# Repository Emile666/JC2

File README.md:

# Junior Computer 2 (JC ][)
Junior-Computer-2 Hardware and Software projects.

# History
The Junior computer design was published by Elektuur/Elektor from 1980 on. It was developed by Loys Nachtmann. The Junior computer is more or less a copy of the original KIM-1 single board computer.

Fourty years later, Joerg Walke created the Junior-Computer 2, which is an expanded version of the original Junior Computer. It contained 32 KB RAM, 8KB ROM and an onboard RS232 serial interface. The development of the Junior Computer 2 is still in progress and you can read all about it on the web-site of Joerg: https://old-computer-tech.net/junior-computer/

Up until now Joerg created the JC2-board (v3.1b), the IO-Basic card, the JC2 backplane card and the Floppy-Graphics (FGC) card.

I became enthusiastic about all the excellent hardware and software Joerg developed and decided to built these boards and then to create add-ons, both hardware and software.

This page serves as a placeholder for all hardware and software projects that I created. It is all open-source, so enjoy!

# Hardware projects

Hardware projects are (mostly) created with KiCad 8 and I publish both the KiCad project-files as the Gerber files. The Gerber files can be sent directly to a PCB manufacturer.

Since these projects nearly always contain a GAL or CPLD, the .pld files describing the programmable logic is also included. I typically use an ATF16V8, an ATF22V10 or an ATF1504 (plcc44 and plcc84). They are programmed with WinCUPL and the .pld file can be loaded directly into WinCUPL. The resulting .jed file is either programmed into the GAL / CPLD directly with the Afterburner programmer (ATF16V8 and ATF22V10), or further processed by ATMISP (to create a .svf file from the .jed file) and svf2xsvf502 (to create a .xsvf file from the .svf file) and then programmed by the Afterburner programmer into the device (ATF1504). A detailed walk-through for an ATF1504 is found [here](./atf1504_program_aftb.md).

- [RAM-bank add-on](./Hardware/rambank): I created a 512K add-on board for the JC2 which contains a AS6C4008 512Kx8 SRAM and a ATF1504 plcc44 GAL. It contains a memory management unit (MMU) register that can switch Monitor ROM, BIOS ROM and the different RAM-banks (28 banks of 16K each). Current version is made with Eagle, never revisions are planned to be made with KiCad.
- [Compact-Flash IDE interface](./Hardware/cf_ide): The idea originated from the Atari XL CF-IDE interface. I changed it for the JC2. Most of the TTL ICs were removed and put into a GAL (an ATF16V8).
- [Backplane](./Hardware/backplane/): I created an update of Joerg's original backplane and added a flat-cable connector to it, so that you can have multiple backplanes connected together.
- [Main-Board](./Hardware/main_board/): I created an update of Joerg's original v3.1b main-board, most notable changes are: 1) one integrated eprom combining Monitor, Basic and BIOS 2) ATF1504 MMU added that supports 512K RAM with 28 RAM-banks of 16K each 3) Monitor, BIOS and Basic ROM are now switchable from MMU, enabling RAM behind it 4) Additional 6522 VIA 5) UART-to-USB bridge added.
- [IO2-Board](./Hardware/IO2/): I created an update of Joerg's original rev. 1D IO-board, most notable changes are: 1) BASIC eprom moved to JC2 main-board and removed all diode-based logic 2) removed papertape reader, Datasette interface and ASCII-keyboard 3) Added 3 x 16-bits IO with MCP23017 ICs 4) Added SPI RAM (1024 Kb)  and I2C eeprom (512 Kb) 5) Added PCF8591 8-bit ADC and DAC 6) Added One-Wire Interface with DS2482 7) Added CF-IDE Interface 8) Level-shifting with BSS138 board instead of 74LVC245.

# Software projects

Software projects are written in 6502 assembly language and are assembled with the Mad-Assembler (MADS), https://mads.atari8.info/. I call MADS from the Windows command-line with mads <filename.asm> -l:<filename.lst> -o:<filename.bin>. This makes sure that you get a decent list-file and the .bin file that can be uploaded to the JC2 using the XMODEM protocol.

- [Memory-test](./Software/memtest): The memory-test program scans the hardware present and detects if a MMU is present. It shows and tests all available RAM and ROM memory, displays the number of RAM-banks found and tests each one of them.
- [Monitor](./Software/jc2_mon_1K): This is the original monitor program written by A. Nachtmann (1980), which was restored and adapted for TASM by A.J. Prosman (2019). I adapted the source for MADS (2024). Included here for reference.
- [JC2-DOS65](./Software/jc2_dos65): Joerg made a v0.2.0 version that supported the SD-card. This version here is a further development and now supports the CF-IDE Interface.
- [JC2-1-EPROM](./Software/jc2_1_eprom): This software integrates BASIC, BIOS and Monitor ROM into a single EPROM version. It already includes the CF-IDE drivers and is supported by a RAM-loader for testing without directly creating a new EPROM version.

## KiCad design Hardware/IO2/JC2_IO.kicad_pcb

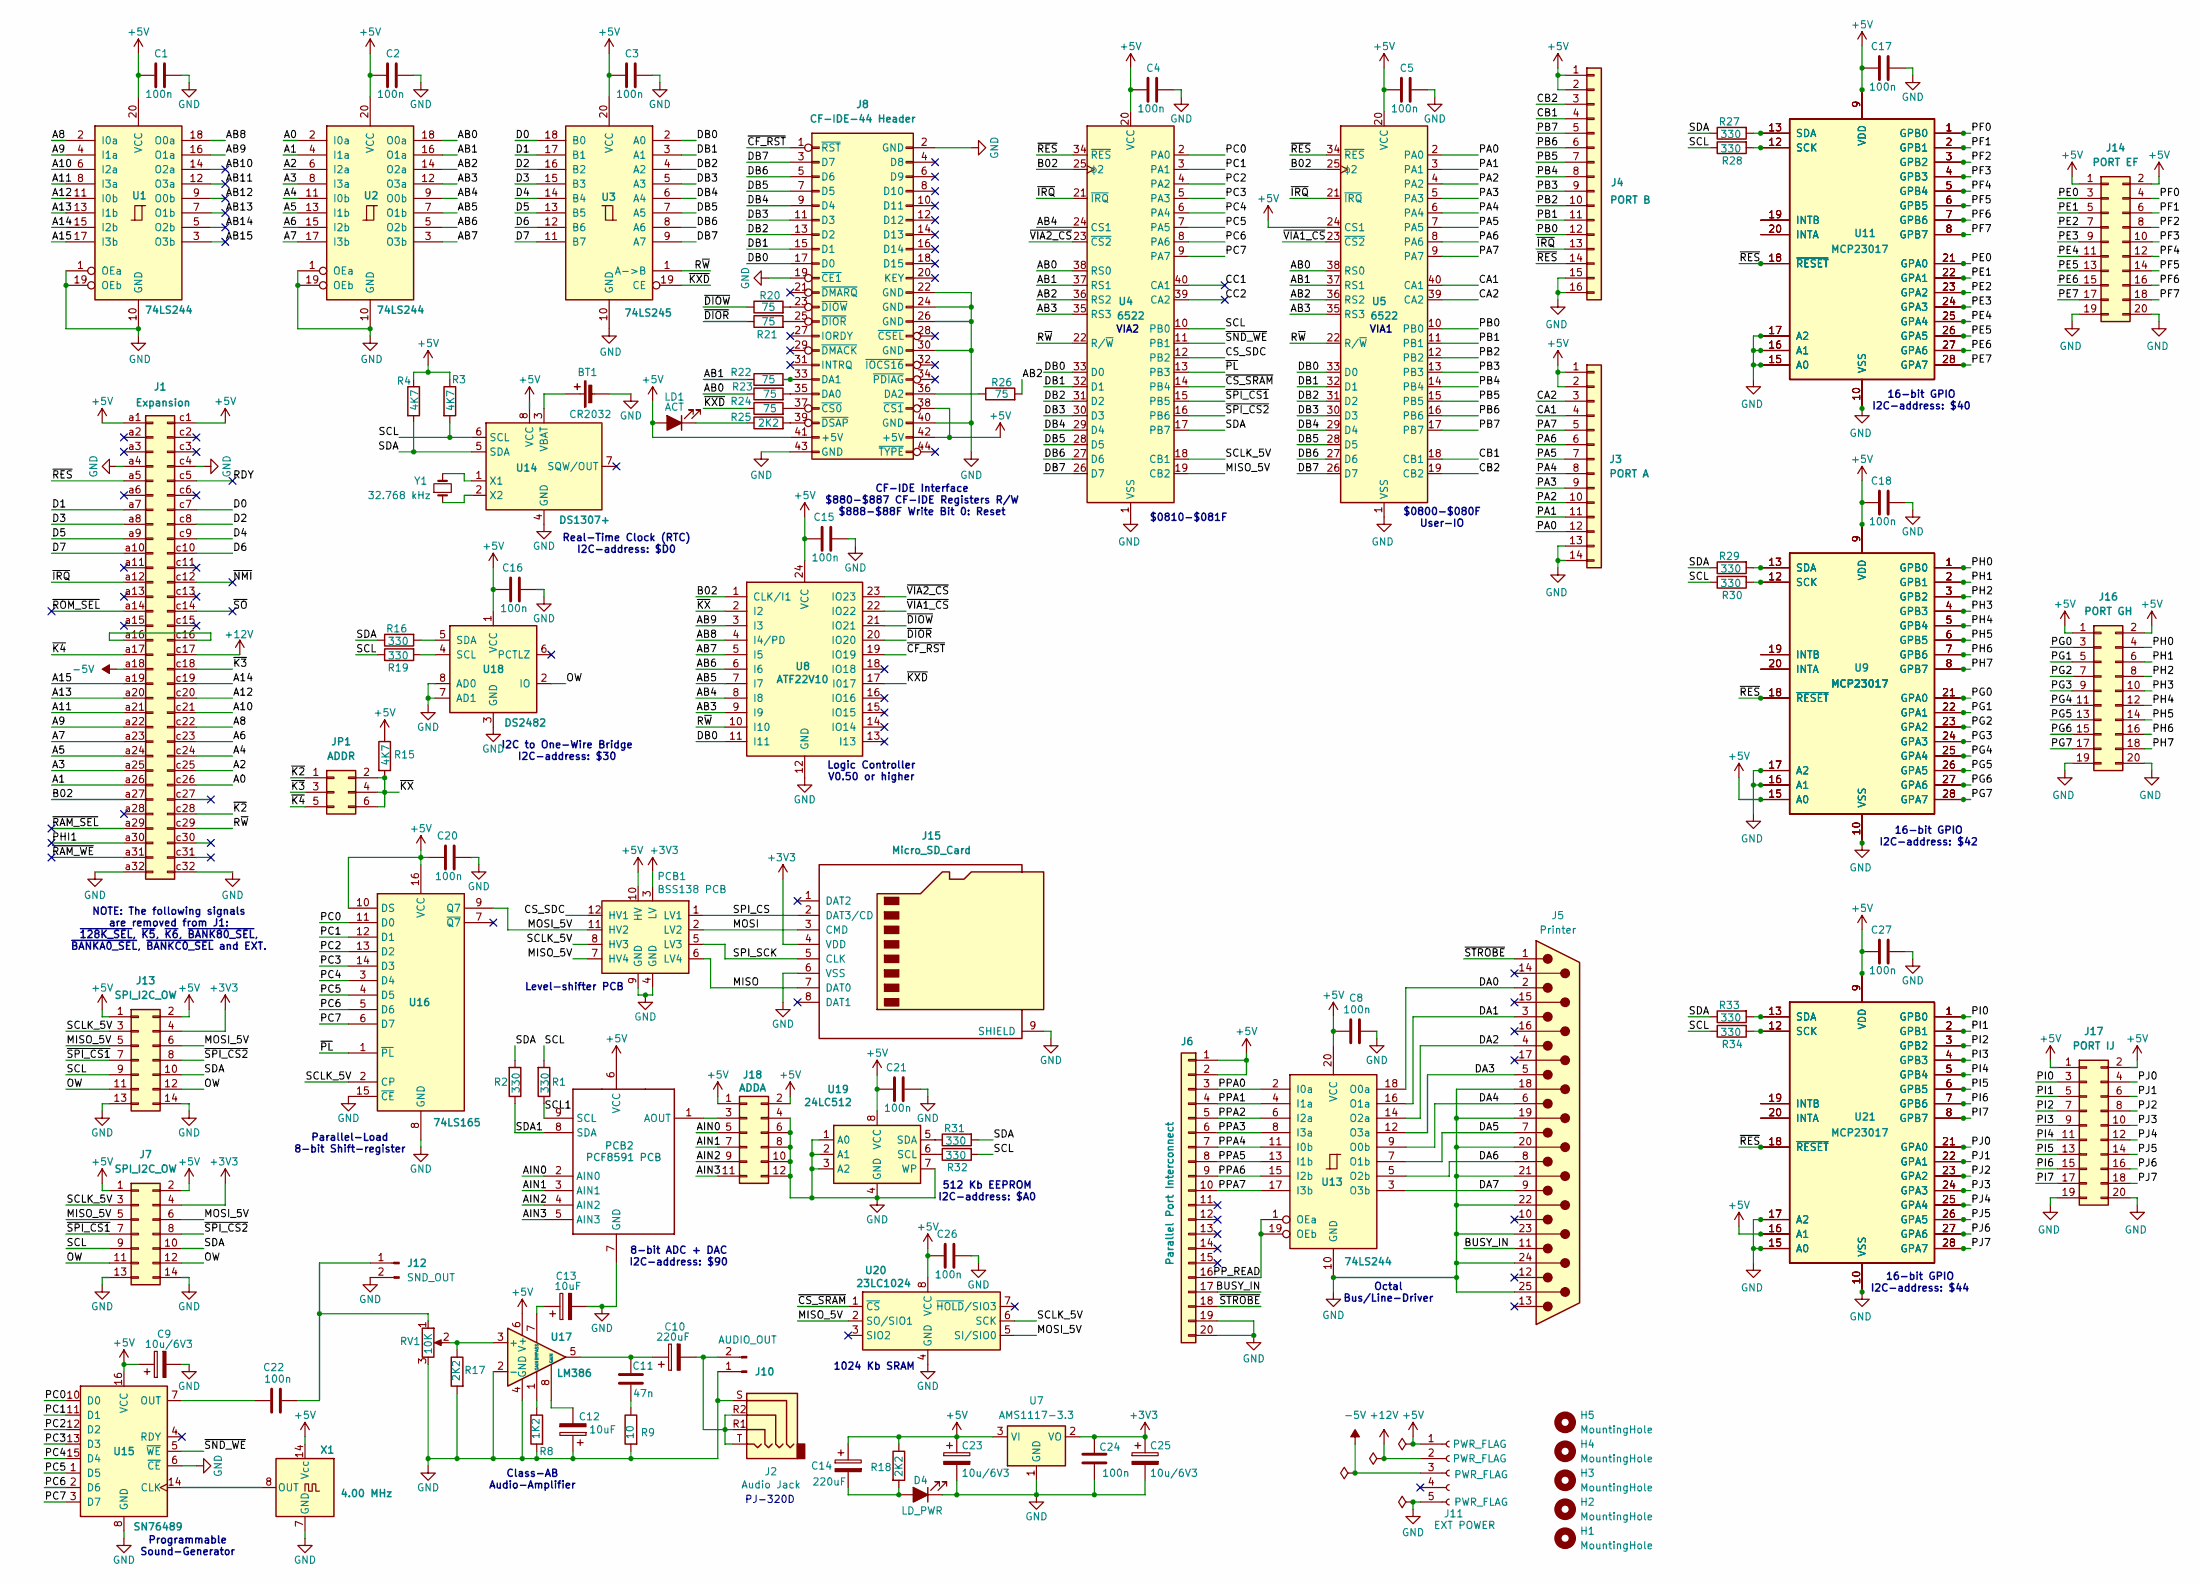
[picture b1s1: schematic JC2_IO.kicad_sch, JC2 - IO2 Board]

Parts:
BT1: CR2032; BatteryHolder_Keystone_107_1x23mm
C1, C2, C3, C4, C5, C8, C15, C16, C17, C18, C20, C21, C22, C24, C26, C27: 100n; C_Rect_L4.6mm_W2.0mm_P2.50mm_MKS02_FKP02
C9, C23, C25: 10u/6V3; CP_Radial_D5.0mm_P2.00mm
C10, C14: 220uF; CP_Radial_D8.0mm_P5.00mm
C11: 47n; C_Rect_L4.6mm_W2.0mm_P2.50mm_MKS02_FKP02
C12, C13: 10uF; CP_Radial_D5.0mm_P2.00mm
D4: LD_PWR; LED_D3.0mm
H1, H2, H3, H4, H5: MountingHole; MountingHole_4.3mm_M4
J1: Expansion; DIN41612_C_2x32_Male_Horizontal_THT
J2: Audio Jack; Jack_3.5mm_PJ320D_Horizontal
J3: PORT A; PinSocket_2x07_P2.54mm_Horizontal
J4: PORT B; PinHeader_2x08_P2.54mm_Horizontal
J5: Printer; DSUB-25_Female_Horizontal_P2.77x2.84mm_EdgePinOffset4.94mm_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
J6: Parallel Port Interconnect; IDC-Header_2x10_P2.54mm_Vertical
J7, J13: SPI_I2C_OW; PinHeader_2x07_P2.54mm_Vertical
J8: CF-IDE-44 Header; PinHeader_2x22_P2.00mm_Vertical
J10: AUDIO_OUT; PinHeader_2x01_P2.54mm_Vertical
J11: EXT POWER; PinHeader_1x05_P2.54mm_Vertical
J12: SND_OUT; PinHeader_2x01_P2.54mm_Vertical
J14: PORT EF; PinHeader_2x10_P2.54mm_Vertical
J15: Micro_SD_Card; SD_Card-micro_socket_A
J16: PORT GH; PinHeader_2x10_P2.54mm_Vertical
J17: PORT IJ; PinHeader_2x10_P2.54mm_Vertical
J18: ADDA; PinHeader_2x06_P2.54mm_Vertical
JP1: ADDR; PinHeader_2x03_P2.54mm_Vertical
LD1: ACT; LED_1206_3216Metric_Pad1.42x1.75mm_HandSolder
PCB1: BSS138 PCB; DIP-12_W10.16mm
PCB2: PCF8591 PCB; PCF8591_PCB
R1, R2, R16, R19, R27, R28, R29, R30, R31, R32, R33, R34: 330; R_Axial_DIN0207_L6.3mm_D2.5mm_P10.16mm_Horizontal
R3, R4, R15: 4K7; R_Axial_DIN0207_L6.3mm_D2.5mm_P10.16mm_Horizontal
R8: 1K2; R_Axial_DIN0207_L6.3mm_D2.5mm_P10.16mm_Horizontal
R9: 10; R_Axial_DIN0207_L6.3mm_D2.5mm_P10.16mm_Horizontal
R17, R18: 2K2; R_Axial_DIN0207_L6.3mm_D2.5mm_P10.16mm_Horizontal
R20, R21, R22, R23, R24, R26: 75; R_1206_3216Metric_Pad1.30x1.75mm_HandSolder
R25: 2K2; R_1206_3216Metric_Pad1.30x1.75mm_HandSolder
RV1: 10K; Potentiometer_ACP_CA14-H5_Horizontal
U1, U2, U13: 74LS244; DIP-20_W7.62mm_Socket
U3: 74LS245; DIP-20_W7.62mm_Socket
U4, U5: 6522; DIP-40_W15.24mm
U7: AMS1117-3.3; SOT-223-3_TabPin2
U8: ATF22V10; DIP-24_W7.62mm
U9, U11, U21: MCP23017; DIP-28_W7.62mm
U14: DS1307+; DIP-8_W7.62mm
U15: SN76489; CERDIP-16_W7.62mm_SideBrazed_Socket
U16: 74LS165; DIP-16_W7.62mm
U17: LM386; DIP-8_W7.62mm
U18: DS2482; SOIC-8W_5.3x5.3mm_P1.27mm
U19: 24LC512; DIP8_SOIC8
U20: 23LC1024; DIP8_SOIC8
U22: MCP23017; SOIC-28W_7.5x18.7mm_P1.27mm
U23, U24: MCP23017_SO; SOIC-28W_7.5x17.9mm_P1.27mm
X1: 4.00 MHz; Oscillator_DIP-14
Y1: 32.768 kHz; Crystal_C38-LF_D3.0mm_L8.0mm_Horizontal

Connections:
+3V3: C24.1, C25.1, J7.4, J13.4, J15.4 (VDD), PCB1.3 (LV), U7.2 (VO)
+5V: C1.1, C2.1, C3.1, C4.1, C5.1, C8.1, C9.1, C14.1, C15.1, C16.1, C17.1, C18.1, C20.1, C21.1, C23.1, C26.1, C27.1, J1.a1, J1.c1, J3.1, J3.2, J4.1, J4.2, J6.1, J6.2, J7.1, J7.2, J8.38 (~CS1), J8.41 (+5V), J8.42 (+5V), J11.1, J13.1, J13.2, J14.1, J14.2, J16.1, J16.2, J17.1, J17.2, J18.1, J18.2, LD1.2 (A), PCB1.10 (HV), PCB2.6 (VCC), R3.1, R4.1, R15.1, R18.1, U1.20 (VCC), U2.20 (VCC), U3.20 (VCC), U4.20 (VCC), U5.20 (VCC), U5.24 (CS1), U7.3 (VI), U8.24 (VCC), U9.9 (VDD), U9.15 (A0), U11.9 (VDD), U13.20 (VCC), U14.8 (VCC), U15.16 (VCC), U16.10 (DS), U16.16 (VCC), U17.6 (V+), U18.1 (VCC), U19.8 (VCC), U20.8 (VCC), U21.9 (VDD), U21.16 (A1), U22.9 (VDD), U22.15 (A0), U23.9 (VDD), U23.16 (A1), U24.9 (VDD), X1.14 (Vcc)
+12V: J1.c17, J11.2
-5V: J1.a18, J11.3
/A0: J1.c26, U2.2 (I0a)
/A1: J1.a26, U2.4 (I1a)
/A2: J1.c25, U2.6 (I2a)
/A3: J1.a25, U2.8 (I3a)
/A4: J1.c24, U2.11 (I0b)
/A5: J1.a24, U2.13 (I1b)
/A6: J1.c23, U2.15 (I2b)
/A7: J1.a23, U2.17 (I3b)
/A8: J1.c22, U1.2 (I0a)
/A9: J1.a22, U1.4 (I1a)
/A10: J1.c21, U1.6 (I2a)
/A11: J1.a21, U1.8 (I3a)
/A12: J1.c20, U1.11 (I0b)
/A13: J1.a20, U1.13 (I1b)
/A14: J1.c19, U1.15 (I2b)
/A15: J1.a19, U1.17 (I3b)
/AB0: R23.1, U2.18 (O0a), U4.38 (RS0), U5.38 (RS0)
/AB1: R22.1, U2.16 (O1a), U4.37 (RS1), U5.37 (RS1)
/AB2: R26.2, U2.14 (O2a), U4.36 (RS2), U5.36 (RS2)
/AB3: U2.12 (O3a), U4.35 (RS3), U5.35 (RS3), U8.9 (I9)
/AB4: U2.9 (O0b), U4.24 (CS1), U8.8 (I8)
/AB5: U2.7 (O1b), U8.7 (I7)
/AB6: U2.5 (O2b), U8.6 (I6)
/AB7: U2.3 (O3b), U8.5 (I5)
/AB8: U1.18 (O0a), U8.4 (I4/PD)
/AB9: U1.16 (O1a), U8.3 (I3)
/AB10: U1.14 (O2a)
/AB11: U1.12 (O3a)
/AB12: U1.9 (O0b)
/AB13: U1.7 (O1b)
/AB14: U1.5 (O2b)
/AB15: U1.3 (O3b)
/AIN0: J18.5, PCB2.2 (AIN0)
/AIN1: J18.7, PCB2.3 (AIN1)
/AIN2: J18.9, PCB2.4 (AIN2)
/AIN3: J18.11, PCB2.5 (AIN3)
/B02: J1.a27, U4.25 (ϕ2), U5.25 (ϕ2), U8.1 (CLK/I1)
/BUSY_IN: J5.11, J6.17
/CA1: J3.4, U5.40 (CA1)
/CA2: J3.3, U5.39 (CA2)
/CB1: J4.4, U5.18 (CB1)
/CB2: J4.3, U5.19 (CB2)
/CC1: U4.40 (CA1)
/CC2: U4.39 (CA2)
/CS_SDC: PCB1.12 (HV1), U4.12 (PB2)
/D0: J1.c7, U3.18 (B0)
/D1: J1.a7, U3.17 (B1)
/D2: J1.c8, U3.16 (B2)
/D3: J1.a8, U3.15 (B3)
/D4: J1.c9, U3.14 (B4)
/D5: J1.a9, U3.13 (B5)
/D6: J1.c10, U3.12 (B6)
/D7: J1.a10, U3.11 (B7)
/DA0: J5.2, U13.18 (O0a)
/DA1: J5.3, U13.16 (O1a)
/DA2: J5.4, U13.14 (O2a)
/DA3: J5.5, U13.12 (O3a)
/DA4: J5.6, U13.9 (O0b)
/DA5: J5.7, U13.7 (O1b)
/DA6: J5.8, U13.5 (O2b)
/DA7: J5.9, U13.3 (O3b)
/DB0: J8.17 (D0), U3.2 (A0), U4.33 (D0), U5.33 (D0), U8.11 (I11)
/DB1: J8.15 (D1), U3.3 (A1), U4.32 (D1), U5.32 (D1)
/DB2: J8.13 (D2), U3.4 (A2), U4.31 (D2), U5.31 (D2)
/DB3: J8.11 (D3), U3.5 (A3), U4.30 (D3), U5.30 (D3)
/DB4: J8.9 (D4), U3.6 (A4), U4.29 (D4), U5.29 (D4)
/DB5: J8.7 (D5), U3.7 (A5), U4.28 (D5), U5.28 (D5)
/DB6: J8.5 (D6), U3.8 (A6), U4.27 (D6), U5.27 (D6)
/DB7: J8.3 (D7), U3.9 (A7), U4.26 (D7), U5.26 (D7)
/MISO: J15.7 (DAT0), PCB1.6 (LV4)
/MISO_5V: J7.5, J13.5, PCB1.7 (HV4), U4.19 (CB2), U20.2 (SO/SIO1)
/MOSI: J15.3 (CMD), PCB1.2 (LV2)
/MOSI_5V: J7.6, J13.6, PCB1.11 (HV2), U16.9 (Q7), U20.5 (SI/SIO0)
/OW: J7.11, J7.12, J13.11, J13.12, U18.2 (IO)
/PA0: J3.12, U5.2 (PA0)
/PA1: J3.11, U5.3 (PA1)
/PA2: J3.10, U5.4 (PA2)
/PA3: J3.9, U5.5 (PA3)
/PA4: J3.8, U5.6 (PA4)
/PA5: J3.7, U5.7 (PA5)
/PA6: J3.6, U5.8 (PA6)
/PA7: J3.5, U5.9 (PA7)
/PB0: J4.12, U5.10 (PB0)
/PB1: J4.11, U5.11 (PB1)
/PB2: J4.10, U5.12 (PB2)
/PB3: J4.9, U5.13 (PB3)
/PB4: J4.8, U5.14 (PB4)
/PB5: J4.7, U5.15 (PB5)
/PB6: J4.6, U5.16 (PB6)
/PB7: J4.5, U5.17 (PB7)
/PC0: U4.2 (PA0), U15.10 (D0), U16.11 (D0)
/PC1: U4.3 (PA1), U15.11 (D1), U16.12 (D1)
/PC2: U4.4 (PA2), U15.12 (D2), U16.13 (D2)
/PC3: U4.5 (PA3), U15.13 (D3), U16.14 (D3)
/PC4: U4.6 (PA4), U15.15 (D4), U16.3 (D4)
/PC5: U4.7 (PA5), U15.1 (D5), U16.4 (D5)
/PC6: U4.8 (PA6), U15.2 (D6), U16.5 (D6)
/PC7: U4.9 (PA7), U15.3 (D7), U16.6 (D7)
/PE0: J14.3, U11.21 (GPA0), U24.21 (GPA0)
/PE1: J14.5, U11.22 (GPA1), U24.22 (GPA1)
/PE2: J14.7, U11.23 (GPA2), U24.23 (GPA2)
/PE3: J14.9, U11.24 (GPA3), U24.24 (GPA3)
/PE4: J14.11, U11.25 (GPA4), U24.25 (GPA4)
/PE5: J14.13, U11.26 (GPA5), U24.26 (GPA5)
/PE6: J14.15, U11.27 (GPA6), U24.27 (GPA6)
/PE7: J14.17, U11.28 (GPA7), U24.28 (GPA7)
/PF0: J14.4, U11.1 (GPB0), U24.1 (GPB0)
/PF1: J14.6, U11.2 (GPB1), U24.2 (GPB1)
/PF2: J14.8, U11.3 (GPB2), U24.3 (GPB2)
/PF3: J14.10, U11.4 (GPB3), U24.4 (GPB3)
/PF4: J14.12, U11.5 (GPB4), U24.5 (GPB4)
/PF5: J14.14, U11.6 (GPB5), U24.6 (GPB5)
/PF6: J14.16, U11.7 (GPB6), U24.7 (GPB6)
/PF7: J14.18, U11.8 (GPB7), U24.8 (GPB7)
/PG0: J16.3, U9.21 (GPA0), U22.21 (GPA0)
/PG1: J16.5, U9.22 (GPA1), U22.22 (GPA1)
/PG2: J16.7, U9.23 (GPA2), U22.23 (GPA2)
/PG3: J16.9, U9.24 (GPA3), U22.24 (GPA3)
/PG4: J16.11, U9.25 (GPA4), U22.25 (GPA4)
/PG5: J16.13, U9.26 (GPA5), U22.26 (GPA5)
/PG6: J16.15, U9.27 (GPA6), U22.27 (GPA6)
/PG7: J16.17, U9.28 (GPA7), U22.28 (GPA7)
/PH0: J16.4, U9.1 (GPB0), U22.1 (GPB0)
/PH1: J16.6, U9.2 (GPB1), U22.2 (GPB1)
/PH2: J16.8, U9.3 (GPB2), U22.3 (GPB2)
/PH3: J16.10, U9.4 (GPB3), U22.4 (GPB3)
/PH4: J16.12, U9.5 (GPB4), U22.5 (GPB4)
/PH5: J16.14, U9.6 (GPB5), U22.6 (GPB5)
/PH6: J16.16, U9.7 (GPB6), U22.7 (GPB6)
/PH7: J16.18, U9.8 (GPB7), U22.8 (GPB7)
/PHI1: J1.a30
/PI0: J17.3, U21.1 (GPB0), U23.1 (GPB0)
/PI1: J17.5, U21.2 (GPB1), U23.2 (GPB1)
/PI2: J17.7, U21.3 (GPB2), U23.3 (GPB2)
/PI3: J17.9, U21.4 (GPB3), U23.4 (GPB3)
/PI4: J17.11, U21.5 (GPB4), U23.5 (GPB4)
/PI5: J17.13, U21.6 (GPB5), U23.6 (GPB5)
/PI6: J17.15, U21.7 (GPB6), U23.7 (GPB6)
/PI7: J17.17, U21.8 (GPB7), U23.8 (GPB7)
/PJ0: J17.4, U21.21 (GPA0), U23.21 (GPA0)
/PJ1: J17.6, U21.22 (GPA1), U23.22 (GPA1)
/PJ2: J17.8, U21.23 (GPA2), U23.23 (GPA2)
/PJ3: J17.10, U21.24 (GPA3), U23.24 (GPA3)
/PJ4: J17.12, U21.25 (GPA4), U23.25 (GPA4)
/PJ5: J17.14, U21.26 (GPA5), U23.26 (GPA5)
/PJ6: J17.16, U21.27 (GPA6), U23.27 (GPA6)
/PJ7: J17.18, U21.28 (GPA7), U23.28 (GPA7)
/PPA0: J6.3, U13.2 (I0a)
/PPA1: J6.4, U13.4 (I1a)
/PPA2: J6.5, U13.6 (I2a)
/PPA3: J6.6, U13.8 (I3a)
/PPA4: J6.7, U13.11 (I0b)
/PPA5: J6.8, U13.13 (I1b)
/PPA6: J6.9, U13.15 (I2b)
/PPA7: J6.10, U13.17 (I3b)
/PP_READ: J6.16, U13.1 (OEa), U13.19 (OEb)
/RDY: J1.c5
/R~W: J1.c29, U3.1 (A->B), U4.22 (R/~W), U5.22 (R/~W), U8.10 (I10)
/SCL: J7.9, J13.9, R1.2, R3.2, R19.1, R28.1, R30.1, R32.2, R34.1, U4.10 (PB0), U14.6 (SCL)
/SCL1: PCB2.9 (SCL), R1.1
/SCLK_5V: J7.3, J13.3, PCB1.8 (HV3), U4.18 (CB1), U16.2 (CP), U20.6 (SCK)
/SDA: J7.10, J13.10, R2.2, R4.2, R16.1, R27.1, R29.1, R31.2, R33.1, U4.17 (PB7), U14.5 (SDA)
/SDA1: PCB2.8 (SDA), R2.1
/SPI_CS: J15.2 (DAT3/CD), PCB1.1 (LV1)
/SPI_SCK: J15.5 (CLK), PCB1.5 (LV3)
/~CF_RST: J8.1 (~RST), U8.19 (IO19)
/~CS_SRAM: U4.14 (PB4), U20.1 (~CS)
/~DIOR: R21.1, U8.20 (IO20)
/~DIOW: R20.1, U8.21 (IO21)
/~IRQ: J1.a12, J4.13, U4.21 (~IRQ), U5.21 (~IRQ)
/~K2: J1.c28, JP1.1
/~K3: J1.c18, JP1.3
/~K4: J1.a17, JP1.5
/~KXD: R24.1, U3.19 (CE), U8.17 (I017)
/~KX: JP1.2, JP1.4, JP1.6, R15.2, U8.2 (I2)
/~NMI: J1.c12
/~PL: U4.13 (PB3), U16.1 (~PL)
/~RAM_SEL: J1.a29
/~RAM_WE: J1.a31
/~RES: J1.a5, J4.14, U4.34 (~RES), U5.34 (~RES), U9.18 (~RESET), U11.18 (~RESET), U21.18 (~RESET), U22.18 (~RESET), U23.18 (~RESET), U24.18 (~RESET)
/~ROM_SEL: J1.a14
/~SND_WE: U4.11 (PB1), U15.5 (~WE)
/~SO: J1.c14
/~SPI_CS1: J7.7, J13.7, U4.15 (PB5)
/~SPI_CS2: J7.8, J13.8, U4.16 (PB6)
/~STROBE: J5.1, J6.18
/~VIA1_CS: U5.23 (~CS2), U8.22 (IO22)
/~VIA2_CS: U4.23 (~CS2), U8.23 (IO23)
GND: BT1.2 (-), C1.2, C2.2, C3.2, C4.2, C5.2, C8.2, C9.2, C12.1, C13.2, C15.2, C16.2, C17.2, C18.2, C20.2, C21.2, C23.2, C24.2, C25.2, C26.2, C27.2, D4.1 (K), J1.a4, J1.a32, J1.c4, J1.c32, J2.S, J3.13, J3.14, J4.15, J4.16, J5.18, J5.19, J5.20, J5.21, J5.22, J5.23, J5.24, J5.25, J6.19, J6.20, J7.13, J7.14, J8.2 (GND), J8.19 (~CE1), J8.22 (GND), J8.24 (GND), J8.26 (GND), J8.30 (GND), J8.40 (GND), J8.43 (GND), J10.1, J11.5, J12.2, J13.13, J13.14, J14.19, J14.20, J15.6 (VSS), J15.9 (SHIELD), J16.19, J16.20, J17.19, J17.20, J18.4, J18.6, J18.8, J18.10, J18.12, PCB1.4 (GND), PCB1.9 (GND), PCB2.7 (GND), R8.2, R9.2, R17.2, RV1.3, U1.1 (OEa), U1.10 (GND), U1.19 (OEb), U2.1 (OEa), U2.10 (GND), U2.19 (OEb), U3.10 (GND), U4.1 (VSS), U5.1 (VSS), U7.1 (GND), U8.12 (GND), U9.10 (VSS), U9.16 (A1), U9.17 (A2), U11.10 (VSS), U11.15 (A0), U11.16 (A1), U11.17 (A2), U13.10 (GND), U14.4 (GND), U15.6 (~CE), U15.8 (GND), U16.8 (GND), U16.15 (~CE), U17.2 (-), U17.4 (GND), U18.3 (GND), U18.7 (AD1), U18.8 (AD0), U19.1 (A0), U19.2 (A1), U19.3 (A2), U19.4 (GND), U19.7 (WP), U20.4 (GND), U21.10 (VSS), U21.15 (A0), U21.17 (A2), U22.10 (VSS), U22.16 (A1), U22.17 (A2), U23.10 (VSS), U23.15 (A0), U23.17 (A2), U24.10 (VSS), U24.15 (A0), U24.16 (A1), U24.17 (A2), X1.7 (GND)
unnamed: BT1.1 (+), U14.3 (VBAT)
unnamed: C10.1, C11.2, U17.5
unnamed: C11.1, R9.1
unnamed: C12.2, U17.8 (GAIN)
unnamed: C14.2, D4.2 (A), R18.2
unnamed: J1.a16, J1.c16
unnamed: J8.35 (DA0), R23.2
unnamed: J8.33 (DA1), R22.2
unnamed: J8.36 (DA2), R26.1
unnamed: J8.37 (~CS0), R24.2
unnamed: J8.25 (~DIOR), R21.2
unnamed: J8.23 (~DIOW), R20.2
unnamed: J8.39 (~DSAP), R25.2
unnamed: C10.2, J2.R1, J2.R2, J2.T, J10.2
unnamed: C22.2, J12.1, RV1.1
unnamed: J18.3, PCB2.1 (AOUT)
unnamed: LD1.1 (K), R25.1
unnamed: R8.1, U17.1 (GAIN)
unnamed: U11.20 (INTA), U24.20 (INTA)
unnamed: U11.19 (INTB), U24.19 (INTB)
unnamed: R28.2, U11.12 (SCK), U24.12 (SCK)
unnamed: R27.2, U11.13 (SDA), U24.13 (SDA)
unnamed: U14.1 (X1), Y1.2
unnamed: U14.2 (X2), Y1.1
unnamed: U15.14 (CLK), X1.8 (OUT)
unnamed: C22.1, U15.7 (OUT)
unnamed: R17.1, RV1.2, U17.3 (+)
unnamed: C13.1, U17.7 (BYPASS)
unnamed: R19.2, U18.4 (SCL)
unnamed: R16.2, U18.5 (SDA)
unnamed: R32.1, U19.6 (SCL)
unnamed: R31.1, U19.5 (SDA)
unnamed: U21.20 (INTA), U23.20 (INTA)
unnamed: U21.19 (INTB), U23.19 (INTB)
unnamed: R34.2, U21.12 (SCK), U23.12 (SCK)
unnamed: R33.2, U21.13 (SDA), U23.13 (SDA)
unnamed: U9.20 (INTA), U22.20 (INTA)
unnamed: U9.19 (INTB), U22.19 (INTB)
unnamed: R30.2, U9.12 (SCK), U22.12 (SCK)
unnamed: R29.2, U9.13 (SDA), U22.13 (SDA)

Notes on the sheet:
VIA2
512 Kb EEPROM I2C-address: $A0
Programmable Sound-Generator
PJ-320D
16-bit GPIO I2C-address: $40
8-bit ADC + DAC I2C-address: $90
CF-IDE Interface $880-$887 CF-IDE Registers R/W $888-$88F Write Bit 0: Reset
Parallel-Load 8-bit Shift-register
Logic Controller V0.50 or higher
Level-shifter PCB
VIA1
1024 Kb SRAM
16-bit GPIO I2C-address: $44
I2C to One-Wire Bridge I2C-address: $30
$0800-$080F User-IO
Real-Time Clock (RTC) I2C-address: $D0
16-bit GPIO I2C-address: $42
Class-AB Audio-Amplifier
NOTE: The following signals are removed from J1: ~{128K_SEL}, ~{K5}, ~{K6}, ~{BANK80_SEL}, ~{BANKA0_SEL}, ~{BANKC0_SEL} and EXT.
Octal Bus/Line-Driver
$0810-$081F

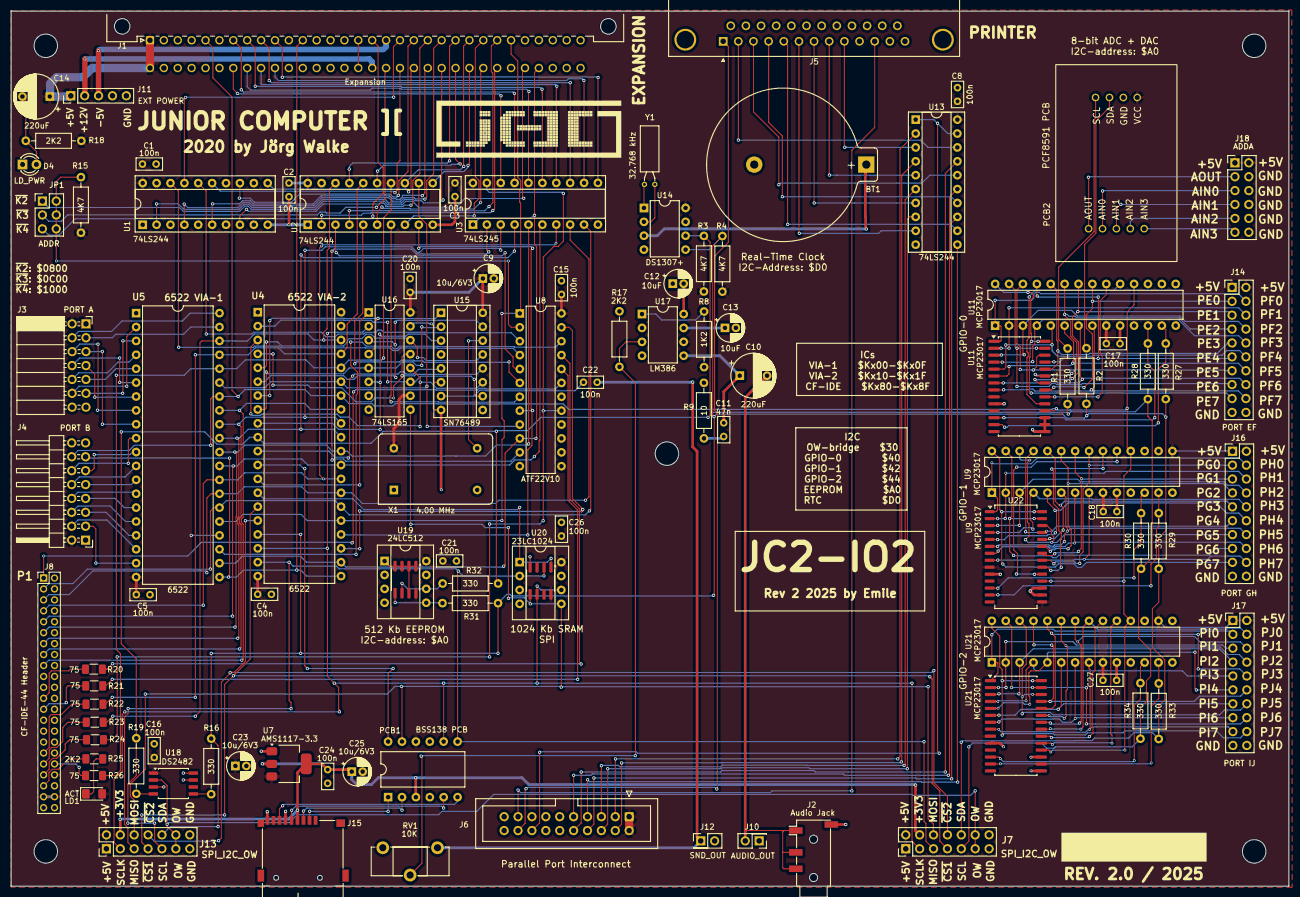
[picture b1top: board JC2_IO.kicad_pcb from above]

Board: 2 copper layers, 233.7 x 160.0 mm, 102 parts (0 on the bottom side), 218 nets.
